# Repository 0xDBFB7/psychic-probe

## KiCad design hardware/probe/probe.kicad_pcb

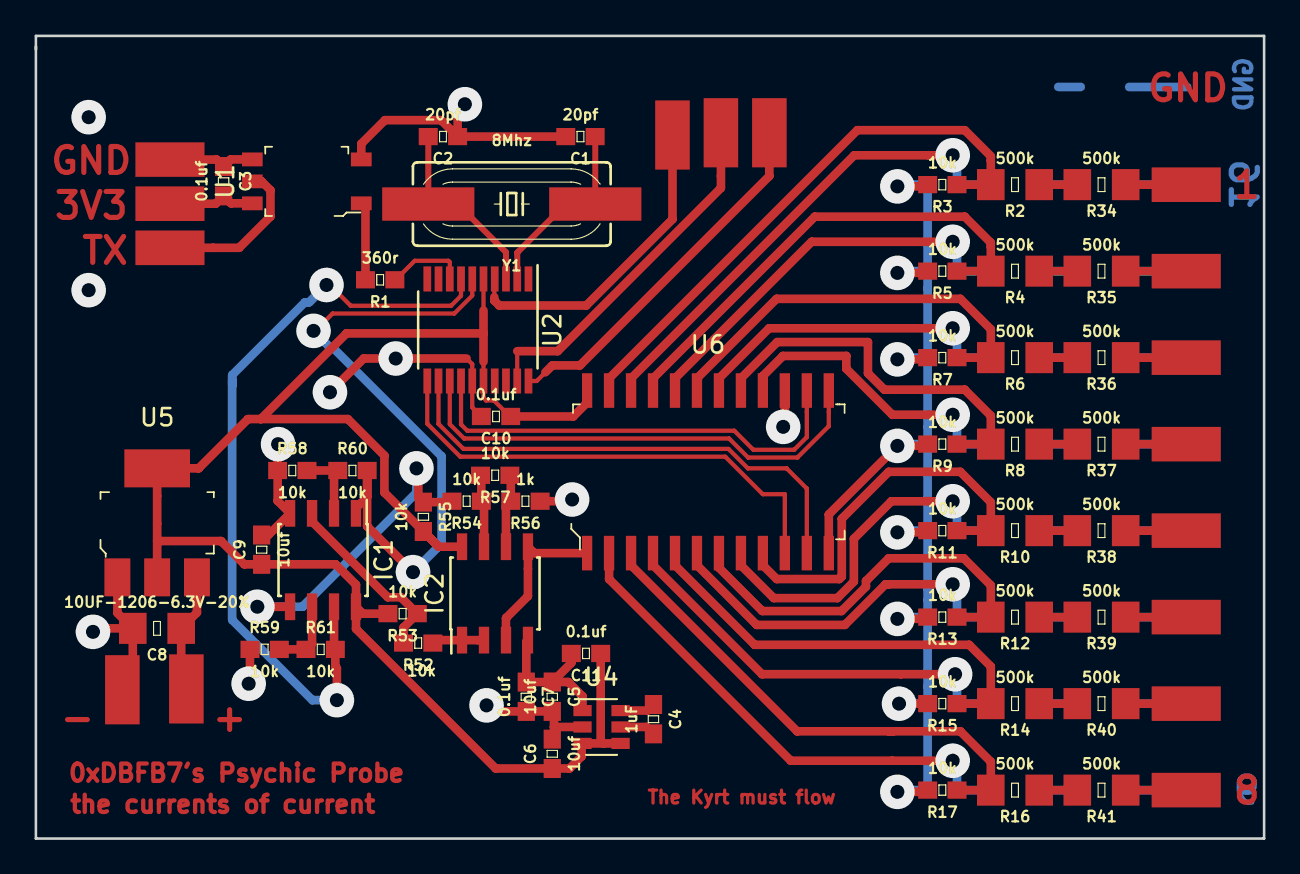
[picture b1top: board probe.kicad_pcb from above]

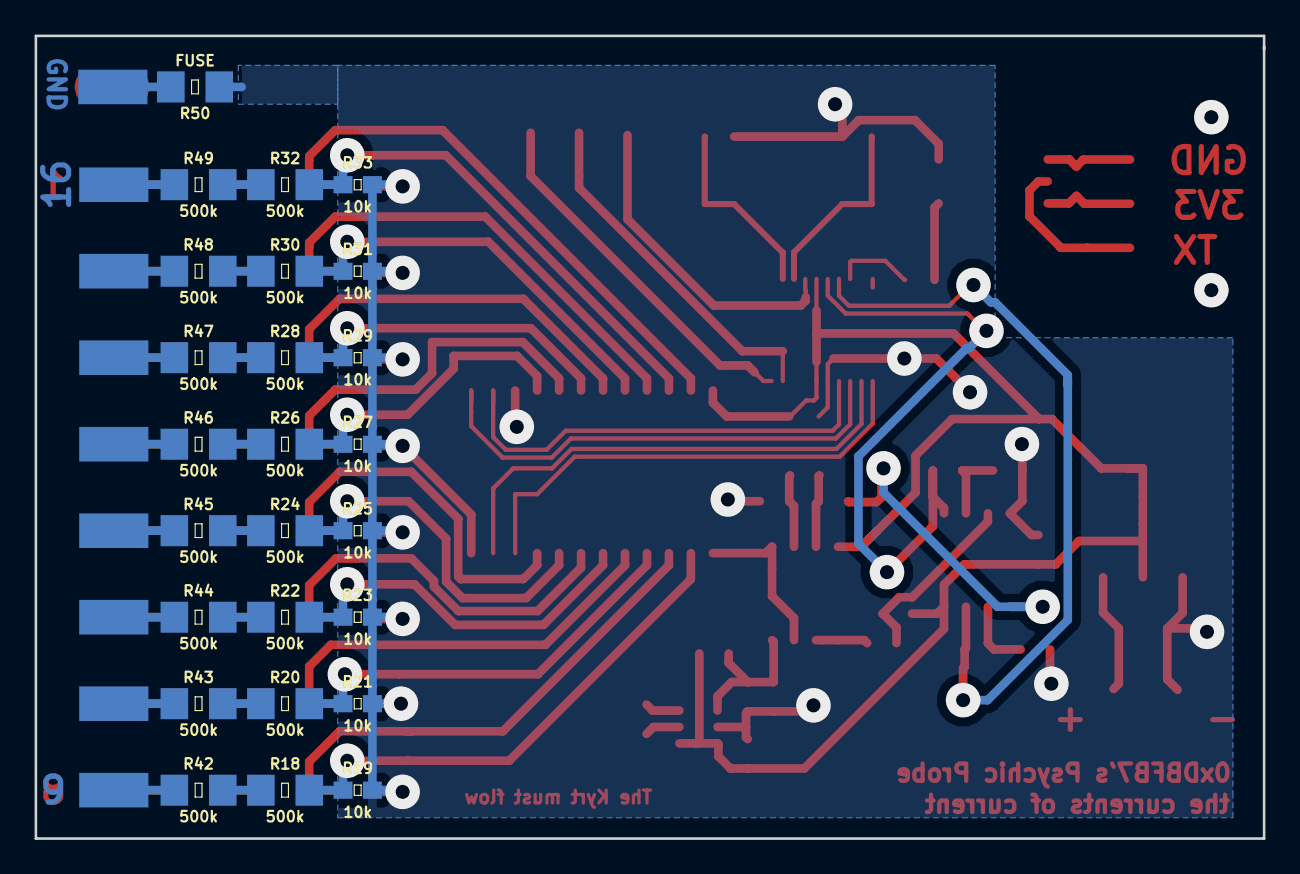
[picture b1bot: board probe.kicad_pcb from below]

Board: 2 copper layers, 71.0 x 46.4 mm, 104 parts (34 on the bottom side), 79 nets.

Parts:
C1, C2: 20pf; 0603
C3, C7, C10, C11: 0.1uf; 0603
C4: 1uF; 0603
C5, C6, C9: 10uf; 0603
C8: 10UF-1206-6.3V-20%; 1206
IC1: TLV9062IDR; SOIC-8_3.9x4.9mm_P1.27mm
IC2: AZ4580; SOIC-8_3.9x4.9mm_P1.27mm
J1, J18, J21, J22: ISOL_3v3; CAP_WIRE_CONNECTION
J2, J3, J4, J5, J6, J7, J8, J9, J10, J11, J12, J13, J14, J15, J16, J17: CONN_01; CAP_WIRE_CONNECTION
J19: ISOL_GND; CAP_WIRE_CONNECTION
J20: ISOL_OUTPUT; CAP_WIRE_CONNECTION
J23: BATT; CAP_WIRE_CONNECTION
J24, J25: GND; CAP_WIRE_CONNECTION
R1: 360r; 0603
R2, R4, R6, R8, R10, R12, R14, R16, R18, R20, R22, R24, R26, R28, R30, R32, R34, R35, R36, R37, R38, R39, R40, R41, R42, R43, R44, R45, R46, R47, R48, R49: 500k; 1206
R3, R5, R7, R9, R11, R13, R15, R17, R19, R21, R23, R25, R27, R29, R31, R33, R52, R53, R54, R55, R57, R58, R59, R60, R61: 10k; 0603
R50: FUSE; 1206
R56: 1k; 0603
U1: TLP2361; SOIC-6-5_W4.55mm
U2: STM32F030F4Px; TSSOP-20_4.4x6.5mm_P0.65mm
U4: LM2776; SOT-23-6
U5: AZ1117; SOT-223
U6: CD74HC4067M96; SOIC-24_W7.50mm
Y1: 8Mhz; HC49UP

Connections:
+3.3V: C6.1, C9.1, C10.1, C11.1, IC1.8, IC2.8, R53.2, R55.2, U2.5, U2.16, U4.3, U4.4, U5.2, U5.4, U6.24
-3V3: C5.1, C7.1, C11.2, IC2.4, U4.1
/BATT: C8.1, J23.1, U5.3
/Dividers/OUT1: R2.2, R3.1, U6.23
/Dividers/OUT2: R4.2, R5.1, U6.21
/Dividers/OUT3: R6.2, R7.1, U6.19
/Dividers/OUT4: R8.2, R9.1, U6.17
/Dividers/OUT5: R10.2, R11.1, U6.9
/Dividers/OUT6: R12.2, R13.1, U6.7
/Dividers/OUT7: R14.2, R15.1, U6.5
/Dividers/OUT8: R16.2, R17.1, U6.3
/Dividers/OUT9: R18.2, R19.1, U6.2
/Dividers/OUT10: R20.2, R21.1, U6.4
/Dividers/OUT11: R22.2, R23.1, U6.6
/Dividers/OUT12: R24.2, R25.1, U6.8
/Dividers/OUT13: R26.2, R27.1, U6.16
/Dividers/OUT14: R28.2, R29.1, U6.18
/Dividers/OUT15: R30.2, R31.1, U6.20
/Dividers/OUT16: R32.2, R33.1, U6.22
/ISOL_3v3: C3.2, J18.1, U1.6
/ISOL_GND: C3.1, J19.1, U1.4
/ISOL_OUTPUT: J20.1, U1.5
/MUX_OUT: IC2.3, IC2.5, U6.1
/RESET: J1.1, U2.4
/S0: U2.11, U6.10
/S1: U2.12, U6.11
/S2: U2.13, U6.13
/S3: U2.14, U6.14
/SHIFTED_x1: IC1.1, R60.2, U2.6
/SHIFTED_x10: IC1.7, R61.2, U2.7
/SWCLK: J22.1, U2.20
/SWDIO: J21.1, U2.19
/UART_TX: R1.1, U2.8
GND: C1.2, C2.1, C5.2, C6.2, C7.2, C8.2, C9.2, C10.2, IC1.4, J24.1, R3.2, R5.2, R7.2, R9.2, R11.2, R13.2, R15.2, R17.2, R19.2, R21.2, R23.2, R25.2, R27.2, R29.2, R31.2, R33.2, R50.1, R56.1, R58.1, R59.1, U1.3, U2.15, U4.2, U5.1, U6.12, U6.15
unnamed: C1.1, U2.2, Y1.1
unnamed: C2.2, U2.3, Y1.2
unnamed: C4.1, U4.6
unnamed: C4.2, U4.5
unnamed: IC1.2, R58.2, R60.1
unnamed: IC1.3, R52.2, R53.1
unnamed: IC1.5, R54.2, R55.1
unnamed: IC1.6, R59.2, R61.1
unnamed: IC2.1, IC2.2, R52.1
unnamed: IC2.6, R56.2, R57.1
unnamed: IC2.7, R54.1, R57.2
unnamed: J2.1, R34.1
unnamed: J3.1, R35.1
unnamed: J4.1, R36.1
unnamed: J5.1, R37.1
unnamed: J6.1, R38.1
unnamed: J7.1, R39.1
unnamed: J8.1, R40.1
unnamed: J9.1, R41.1
unnamed: J10.1, R42.1
unnamed: J11.1, R43.1
unnamed: J12.1, R44.1
unnamed: J13.1, R45.1
unnamed: J14.1, R46.1
unnamed: J15.1, R47.1
unnamed: J16.1, R48.1
unnamed: J17.1, R49.1
unnamed: J25.1, R50.2
unnamed: R1.2, U1.1
unnamed: R2.1, R34.2
unnamed: R10.1, R38.2
unnamed: R12.1, R39.2
unnamed: R14.1, R40.2
unnamed: R16.1, R41.2
unnamed: R18.1, R42.2
unnamed: R20.1, R43.2
unnamed: R22.1, R44.2
unnamed: R24.1, R45.2
unnamed: R26.1, R46.2
unnamed: R28.1, R47.2
unnamed: R30.1, R48.2
unnamed: R32.1, R49.2
unnamed: R4.1, R35.2
unnamed: R6.1, R36.2
unnamed: R8.1, R37.2

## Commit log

2018-12-10 First!
2018-12-16 I think I can simplify the amplifier a bit
2018-12-18 Layout complete!
2019-01-19 Planning on renaming the firmware in STM32Cube
2019-01-19 All renamed properly
2019-01-19 Gitignore broken
2019-01-19 Ah, just needed to dump the cache.
2019-01-19 Optocoupler UART working
2019-01-19 Waiting for PollADC to complete takes way longer than an ADC cycle.
2019-01-19 ADC interrupt functional
2019-01-20 Working on a double buffer setup
2019-01-20 Timing some parts of the code
2019-01-20 There's a substantial amount of jitter in the adc timing.
2019-01-20 Much better.
2019-01-20 All right! Functional.
2019-01-21 Why are 3 and 2 swapped on the schematic? Grrr
2019-01-21 x10 and x1 were also swapped in code.
2019-01-21 Feature complete, as nearly as I can tell
